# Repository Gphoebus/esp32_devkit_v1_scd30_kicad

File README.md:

# esp32_devkit_v1_scd30_kicad
Tout le kicad pour le projet

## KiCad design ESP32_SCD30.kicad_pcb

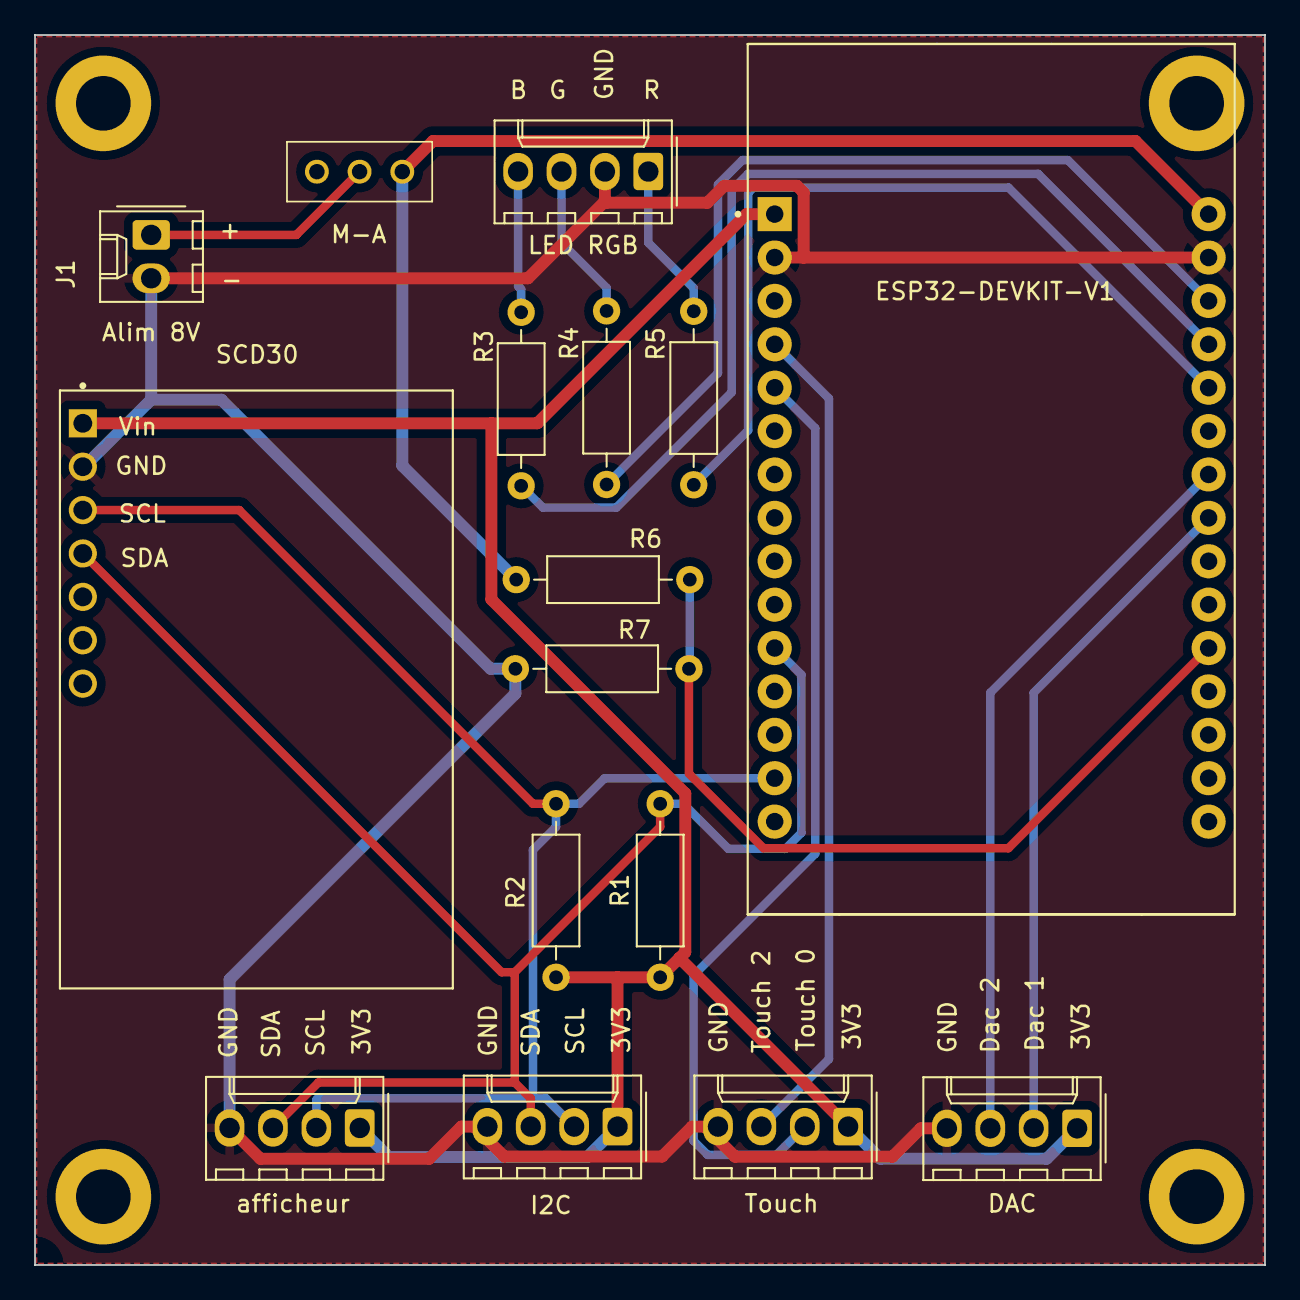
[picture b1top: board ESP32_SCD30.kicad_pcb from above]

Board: 2 copper layers, 72.0 x 72.0 mm, 20 parts (0 on the bottom side), 17 nets.

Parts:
H1, H2, H3, H4: MountingHole; MountingHole_3.2mm_M3_DIN965_Pad
J1: Alim 8V; Molex_KK-254_AE-6410-02A_1x02_P2.54mm_Vertical
J2: afficheur; Molex_KK-254_AE-6410-04A_1x04_P2.54mm_Vertical
J3: I2C; Molex_KK-254_AE-6410-04A_1x04_P2.54mm_Vertical
J4: Touch; Molex_KK-254_AE-6410-04A_1x04_P2.54mm_Vertical
J5: DAC; Molex_KK-254_AE-6410-04A_1x04_P2.54mm_Vertical
LED RGB: LED_RKGB; Molex_KK-254_AE-6410-04A_1x04_P2.54mm_Vertical
R1, R2: 47000R; R_Axial_DIN0207_L6.3mm_D2.5mm_P10.16mm_Horizontal
R3, R4, R5: 180R; R_Axial_DIN0207_L6.3mm_D2.5mm_P10.16mm_Horizontal
R6: 1M; R_Axial_DIN0207_L6.3mm_D2.5mm_P10.16mm_Horizontal
R7: 330k; R_Axial_DIN0207_L6.3mm_D2.5mm_P10.16mm_Horizontal
S1: M-A; SS12D00G3
U1: ESP32-DEVKIT-V1; MODULE_ESP32_DEVKIT_V1
U2: SCD30; MODULE_SCD30

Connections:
3v3: J2.1, J3.1, J4.1, J5.1, R1.1, R2.1, U1.1 (3V3), U2.1 (VDD)
/D12: R3.1, U1.27 (D12)
/D13: R4.1, U1.28 (D13)
/D14: R5.1, U1.26 (D14)
/D35_adc: R6.2, R7.1, U1.20 (D35)
/Dac1: J5.2, U1.23 (D25)
/Dac_2: J5.3, U1.24 (D26)
/SCL: J2.2, J3.2, R2.2, U1.14 (D22), U2.3 (TX/SCL)
/SDA: J2.3, J3.3, R1.2, U1.11 (D21), U2.4 (RX/SDA)
/Touch_0: J4.2, U1.5 (D4)
/Touch_2: J4.3, U1.4 (D2)
GND: J1.2, J2.4, J3.4, J4.4, J5.4, LED RGB.2 (K), R7.2, U1.2 (GND), U1.29 (GND), U2.2 (GND)
unnamed: LED RGB.4 (BA), R3.2
unnamed: LED RGB.3 (GA), R4.2
unnamed: LED RGB.1 (RA), R5.2
unnamed: J1.1, S1.2 (COM)
unnamed: R6.1, S1.3 (NO), U1.30 (VIN)
